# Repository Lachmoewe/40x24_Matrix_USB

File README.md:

40x24_Matrix_USB
================

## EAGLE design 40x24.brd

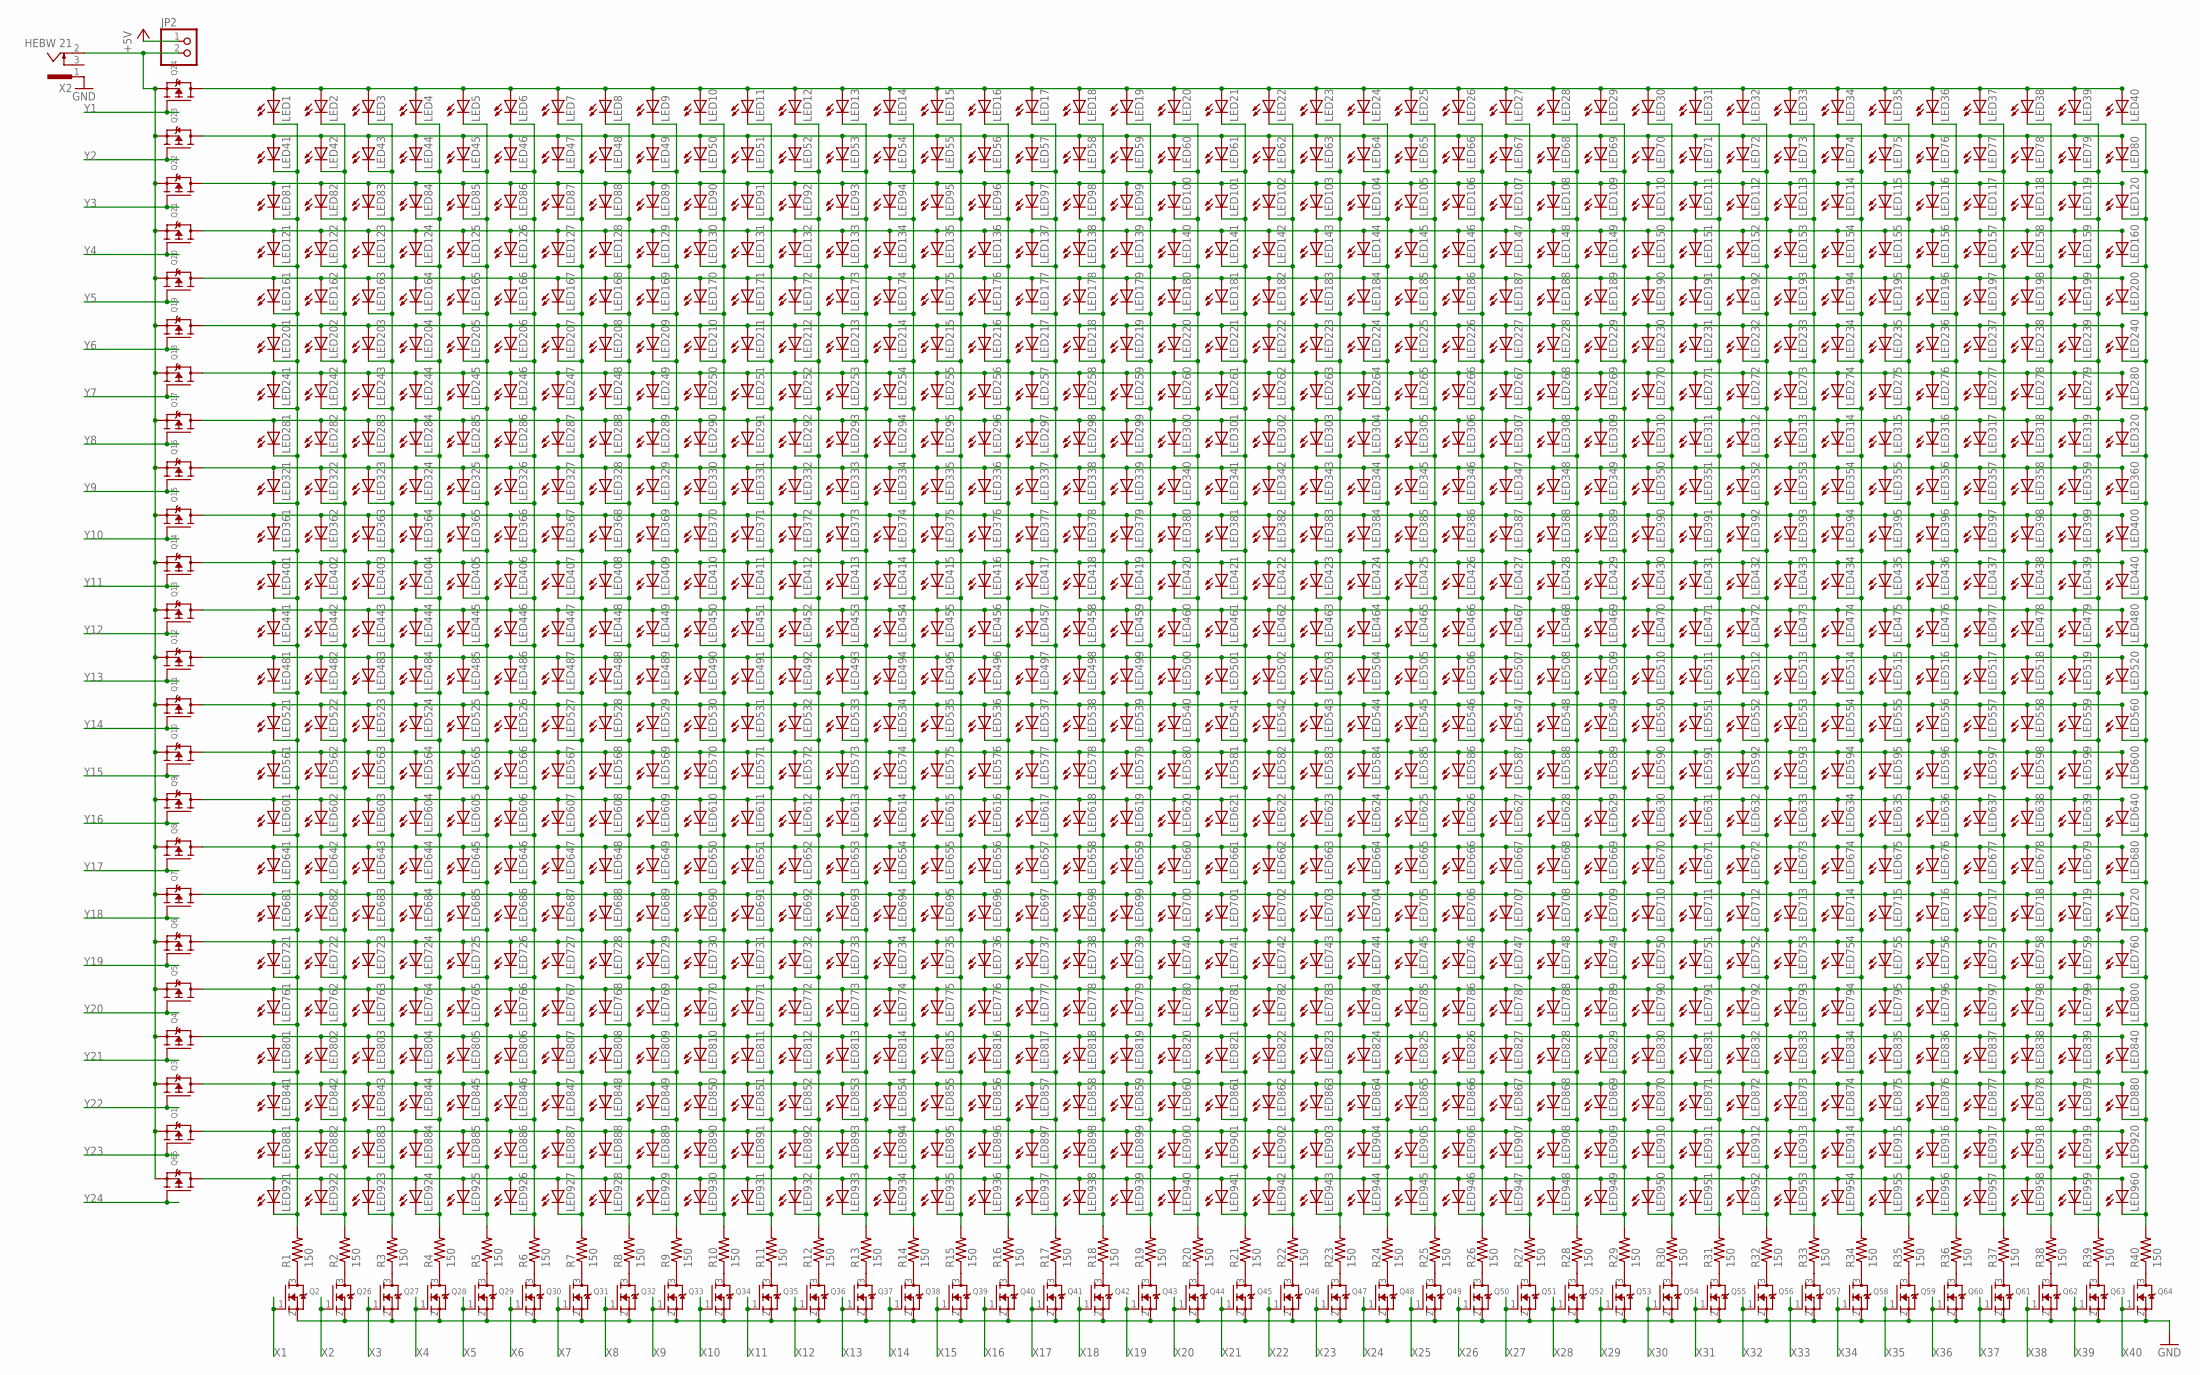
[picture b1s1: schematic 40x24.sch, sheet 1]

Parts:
JP2: PINHD-1X2; 1X02
LED1, LED2, LED3, LED4, LED5, LED6, LED7, LED8, LED9, LED10, LED11, LED12, LED13, LED14, LED15, LED16, LED17, LED18, LED19, LED20, LED21, LED22, LED23, LED24, LED25, LED26, LED27, LED28, LED29, LED30, LED31, LED32, LED33, LED34, LED35, LED36, LED37, LED38, LED39, LED40, LED41, LED42, LED43, LED44, LED45, LED46, LED47, LED48, LED49, LED50, LED51, LED52, LED53, LED54, LED55, LED56, LED57, LED58, LED59, LED60, LED61, LED62, LED63, LED64, LED65, LED66, LED67, LED68, LED69, LED70, LED71, LED72, LED73, LED74, LED75, LED76, LED77, LED78, LED79, LED80, LED81, LED82, LED83, LED84, LED85, LED86, LED87, LED88, LED89, LED90, LED91, LED92, LED93, LED94, LED95, LED96, LED97, LED98, LED99, LED100, LED101, LED102, LED103, LED104, LED105, LED106, LED107, LED108, LED109, LED110, LED111, LED112, LED113, LED114, LED115, LED116, LED117, LED118, LED119, LED120, LED121, LED122, LED123, LED124, LED125, LED126, LED127, LED128, LED129, LED130, LED131, LED132, LED133, LED134, LED135, LED136, LED137, LED138, LED139, LED140, LED141, LED142, LED143, LED144, LED145, LED146, LED147, LED148, LED149, LED150, LED151, LED152, LED153, LED154, LED155, LED156, LED157, LED158, LED159, LED160, LED161, LED162, LED163, LED164, LED165, LED166, LED167, LED168, LED169, LED170, LED171, LED172, LED173, LED174, LED175, LED176, LED177, LED178, LED179, LED180, LED181, LED182, LED183, LED184, LED185, LED186, LED187, LED188, LED189, LED190, LED191, LED192, LED193, LED194, LED195, LED196, LED197, LED198, LED199, LED200, LED201, LED202, LED203, LED204, LED205, LED206, LED207, LED208, LED209, LED210, LED211, LED212, LED213, LED214, LED215, LED216, LED217, LED218, LED219, LED220, LED221, LED222, LED223, LED224, LED225, LED226, LED227, LED228, LED229, LED230, LED231, LED232, LED233, LED234, LED235, LED236, LED237, LED238, LED239, LED240, LED241, LED242, LED243, LED244, LED245, LED246, LED247, LED248, LED249, LED250, LED251, LED252, LED253, LED254, LED255, LED256, LED257, LED258, LED259, LED260, LED261, LED262, LED263, LED264, LED265, LED266, LED267, LED268, LED269, LED270, LED271, LED272, LED273, LED274, LED275, LED276, LED277, LED278, LED279, LED280, LED281, LED282, LED283, LED284, LED285, LED286, LED287, LED288, LED289, LED290, LED291, LED292, LED293, LED294, LED295, LED296, LED297, LED298, LED299, LED300, LED301, LED302, LED303, LED304, LED305, LED306, LED307, LED308, LED309, LED310, LED311, LED312, LED313, LED314, LED315, LED316, LED317, LED318, LED319, LED320, LED321, LED322, LED323, LED324, LED325, LED326, LED327, LED328, LED329, LED330, LED331, LED332, LED333, LED334, LED335, LED336, LED337, LED338, LED339, LED340, LED341, LED342, LED343, LED344, LED345, LED346, LED347, LED348, LED349, LED350, LED351, LED352, LED353, LED354, LED355, LED356, LED357, LED358, LED359, LED360, LED361, LED362, LED363, LED364, LED365, LED366, LED367, LED368, LED369, LED370, LED371, LED372, LED373, LED374, LED375, LED376, LED377, LED378, LED379, LED380, LED381, LED382, LED383, LED384, LED385, LED386, LED387, LED388, LED389, LED390, LED391, LED392, LED393, LED394, LED395, LED396, LED397, LED398, LED399, LED400, LED401, LED402, LED403, LED404, LED405, LED406, LED407, LED408, LED409, LED410, LED411, LED412, LED413, LED414, LED415, LED416, LED417, LED418, LED419, LED420, LED421, LED422, LED423, LED424, LED425, LED426, LED427, LED428, LED429, LED430, LED431, LED432, LED433, LED434, LED435, LED436, LED437, LED438, LED439, LED440, LED441, LED442, LED443, LED444, LED445, LED446, LED447, LED448, LED449, LED450, LED451, LED452, LED453, LED454, LED455, LED456, LED457, LED458, LED459, LED460, LED461, LED462, LED463, LED464, LED465, LED466, LED467, LED468, LED469, LED470, LED471, LED472, LED473, LED474, LED475, LED476, LED477, LED478, LED479, LED480, LED481, LED482, LED483, LED484, LED485, LED486, LED487, LED488, LED489, LED490, LED491, LED492, LED493, LED494, LED495, LED496, LED497, LED498, LED499, LED500, LED501, LED502, LED503, LED504, LED505, LED506, LED507, LED508, LED509, LED510, LED511, LED512, LED513, LED514, LED515, LED516, LED517, LED518, LED519, LED520, LED521, LED522, LED523, LED524, LED525, LED526, LED527, LED528, LED529, LED530, LED531, LED532, LED533, LED534, LED535, LED536, LED537, LED538, LED539, LED540, LED541, LED542, LED543, LED544, LED545, LED546, LED547, LED548, LED549, LED550, LED551, LED552, LED553, LED554, LED555, LED556, LED557, LED558, LED559, LED560, LED561, LED562, LED563, LED564, LED565, LED566, LED567, LED568, LED569, LED570, LED571, LED572, LED573, LED574, LED575, LED576, LED577, LED578, LED579, LED580, LED581, LED582, LED583, LED584, LED585, LED586, LED587, LED588, LED589, LED590, LED591, LED592, LED593, LED594, LED595, LED596, LED597, LED598, LED599, LED600, LED601, LED602, LED603, LED604, LED605, LED606, LED607, LED608, LED609, LED610, LED611, LED612, LED613, LED614, LED615, LED616, LED617, LED618, LED619, LED620, LED621, LED622, LED623, LED624, LED625, LED626, LED627, LED628, LED629, LED630, LED631, LED632, LED633, LED634, LED635, LED636, LED637, LED638, LED639, LED640, LED641, LED642, LED643, LED644, LED645, LED646, LED647, LED648, LED649, LED650, LED651, LED652, LED653, LED654, LED655, LED656, LED657, LED658, LED659, LED660, LED661, LED662, LED663, LED664, LED665, LED666, LED667, LED668, LED669, LED670, LED671, LED672, LED673, LED674, LED675, LED676, LED677, LED678, LED679, LED680, LED681, LED682, LED683, LED684, LED685, LED686, LED687, LED688, LED689, LED690, LED691, LED692, LED693, LED694, LED695, LED696, LED697, LED698, LED699, LED700, LED701, LED702, LED703, LED704, LED705, LED706, LED707, LED708, LED709, LED710, LED711, LED712, LED713, LED714, LED715, LED716, LED717, LED718, LED719, LED720, LED721, LED722, LED723, LED724, LED725, LED726, LED727, LED728, LED729, LED730, LED731, LED732, LED733, LED734, LED735, LED736, LED737, LED738, LED739, LED740, LED741, LED742, LED743, LED744, LED745, LED746, LED747, LED748, LED749, LED750, LED751, LED752, LED753, LED754, LED755, LED756, LED757, LED758, LED759, LED760, LED761, LED762, LED763, LED764, LED765, LED766, LED767, LED768, LED769, LED770, LED771, LED772, LED773, LED774, LED775, LED776, LED777, LED778, LED779, LED780, LED781, LED782, LED783, LED784, LED785, LED786, LED787, LED788, LED789, LED790, LED791, LED792, LED793, LED794, LED795, LED796, LED797, LED798, LED799, LED800, LED801, LED802, LED803, LED804, LED805, LED806, LED807, LED808, LED809, LED810, LED811, LED812, LED813, LED814, LED815, LED816, LED817, LED818, LED819, LED820, LED821, LED822, LED823, LED824, LED825, LED826, LED827, LED828, LED829, LED830, LED831, LED832, LED833, LED834, LED835, LED836, LED837, LED838, LED839, LED840, LED841, LED842, LED843, LED844, LED845, LED846, LED847, LED848, LED849, LED850, LED851, LED852, LED853, LED854, LED855, LED856, LED857, LED858, LED859, LED860, LED861, LED862, LED863, LED864, LED865, LED866, LED867, LED868, LED869, LED870, LED871, LED872, LED873, LED874, LED875, LED876, LED877, LED878, LED879, LED880, LED881, LED882, LED883, LED884, LED885, LED886, LED887, LED888, LED889, LED890, LED891, LED892, LED893, LED894, LED895, LED896, LED897, LED898, LED899, LED900, LED901, LED902, LED903, LED904, LED905, LED906, LED907, LED908, LED909, LED910, LED911, LED912, LED913, LED914, LED915, LED916, LED917, LED918, LED919, LED920, LED921, LED922, LED923, LED924, LED925, LED926, LED927, LED928, LED929, LED930, LED931, LED932, LED933, LED934, LED935, LED936, LED937, LED938, LED939, LED940, LED941, LED942, LED943, LED944, LED945, LED946, LED947, LED948, LED949, LED950, LED951, LED952, LED953, LED954, LED955, LED956, LED957, LED958, LED959, LED960: LED3MM
Q1, Q3, Q4, Q5, Q6, Q7, Q8, Q9, Q10, Q11, Q12, Q13, Q14, Q15, Q16, Q17, Q18, Q19, Q20, Q21, Q22, Q23, Q24, Q65: MOSFET-P; SOT23-R
Q2, Q26, Q27, Q28, Q29, Q30, Q31, Q32, Q33, Q34, Q35, Q36, Q37, Q38, Q39, Q40, Q41, Q42, Q43, Q44, Q45, Q46, Q47, Q48, Q49, Q50, Q51, Q52, Q53, Q54, Q55, Q56, Q57, Q58, Q59, Q60, Q61, Q62, Q63, Q64: MOSFET-NREFLOW; SOT23-R
R1, R2, R3, R4, R5, R6, R7, R8, R9, R10, R11, R12, R13, R14, R15, R16, R17, R18, R19, R20, R21, R22, R23, R24, R25, R26, R27, R28, R29, R30, R31, R32, R33, R34, R35, R36, R37, R38, R39, R40: 150; 0805
X2: HEBW 21; 733980-62

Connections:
+5V: JP2.1; also elsewhere on the board
GND: Q2.2 (S), Q26.2 (S), Q27.2 (S), Q28.2 (S), Q29.2 (S), Q30.2 (S), Q31.2 (S), Q32.2 (S), Q33.2 (S), Q34.2 (S), Q35.2 (S), Q36.2 (S), Q37.2 (S), Q38.2 (S), Q39.2 (S), Q40.2 (S), Q41.2 (S), Q42.2 (S), Q43.2 (S), Q44.2 (S), Q45.2 (S), Q46.2 (S), Q47.2 (S), Q48.2 (S), Q49.2 (S), Q50.2 (S), Q51.2 (S), Q52.2 (S), Q53.2 (S), Q54.2 (S), Q55.2 (S), Q56.2 (S), Q57.2 (S), Q58.2 (S), Q59.2 (S), Q60.2 (S), Q61.2 (S), Q62.2 (S), Q63.2 (S), Q64.2 (S), X2.1; also elsewhere on the board
unnamed: LED1.A, LED2.A, LED3.A, LED4.A, LED5.A, LED6.A, LED7.A, LED8.A, LED9.A, LED10.A, LED11.A, LED12.A, LED13.A, LED14.A, LED15.A, LED16.A, LED17.A, LED18.A, LED19.A, LED20.A, LED21.A, LED22.A, LED23.A, LED24.A, LED25.A, LED26.A, LED27.A, LED28.A, LED29.A, LED30.A, LED31.A, LED32.A, LED33.A, LED34.A, LED35.A, LED36.A, LED37.A, LED38.A, LED39.A, LED40.A, Q24.3 (D)
unnamed: LED81.A, LED82.A, LED83.A, LED84.A, LED85.A, LED86.A, LED87.A, LED88.A, LED89.A, LED90.A, LED91.A, LED92.A, LED93.A, LED94.A, LED95.A, LED96.A, LED97.A, LED98.A, LED99.A, LED100.A, LED101.A, LED102.A, LED103.A, LED104.A, LED105.A, LED106.A, LED107.A, LED108.A, LED109.A, LED110.A, LED111.A, LED112.A, LED113.A, LED114.A, LED115.A, LED116.A, LED117.A, LED118.A, LED119.A, LED120.A, Q22.3 (D)
unnamed: Q2.3 (D), R1.1
unnamed: Q26.3 (D), R2.1
unnamed: LED2.K (C), LED42.K (C), LED82.K (C), LED122.K (C), LED162.K (C), LED202.K (C), LED242.K (C), LED282.K (C), LED322.K (C), LED362.K (C), LED402.K (C), LED442.K (C), LED482.K (C), LED522.K (C), LED562.K (C), LED602.K (C), LED642.K (C), LED682.K (C), LED722.K (C), LED762.K (C), LED802.K (C), LED842.K (C), LED882.K (C), LED922.K (C), R2.2
unnamed: Q27.3 (D), R3.1
unnamed: Q28.3 (D), R4.1
unnamed: Q29.3 (D), R5.1
unnamed: Q30.3 (D), R6.1
unnamed: Q31.3 (D), R7.1
unnamed: Q32.3 (D), R8.1
unnamed: Q33.3 (D), R9.1
unnamed: Q34.3 (D), R10.1
unnamed: Q35.3 (D), R11.1
unnamed: Q36.3 (D), R12.1
unnamed: Q37.3 (D), R13.1
unnamed: Q38.3 (D), R14.1
unnamed: Q39.3 (D), R15.1
unnamed: Q40.3 (D), R16.1
unnamed: Q41.3 (D), R17.1
unnamed: Q42.3 (D), R18.1
unnamed: Q43.3 (D), R19.1
unnamed: Q44.3 (D), R20.1
unnamed: Q45.3 (D), R21.1
unnamed: Q46.3 (D), R22.1
unnamed: Q47.3 (D), R23.1
unnamed: Q48.3 (D), R24.1
unnamed: Q49.3 (D), R25.1
unnamed: Q50.3 (D), R26.1
unnamed: Q51.3 (D), R27.1
unnamed: Q52.3 (D), R28.1
unnamed: Q53.3 (D), R29.1
unnamed: Q54.3 (D), R30.1
unnamed: Q55.3 (D), R31.1
unnamed: Q56.3 (D), R32.1
unnamed: Q57.3 (D), R33.1
unnamed: Q58.3 (D), R34.1
unnamed: Q59.3 (D), R35.1
unnamed: Q60.3 (D), R36.1
unnamed: LED41.A, LED42.A, LED43.A, LED44.A, LED45.A, LED46.A, LED47.A, LED48.A, LED49.A, LED50.A, LED51.A, LED52.A, LED53.A, LED54.A, LED55.A, LED56.A, LED57.A, LED58.A, LED59.A, LED60.A, LED61.A, LED62.A, LED63.A, LED64.A, LED65.A, LED66.A, LED67.A, LED68.A, LED69.A, LED70.A, LED71.A, LED72.A, LED73.A, LED74.A, LED75.A, LED76.A, LED77.A, LED78.A, LED79.A, LED80.A, Q23.3 (D)
unnamed: Q61.3 (D), R37.1
unnamed: Q62.3 (D), R38.1
unnamed: Q63.3 (D), R39.1
unnamed: Q64.3 (D), R40.1
unnamed: JP2.2, Q1.2 (S), Q3.2 (S), Q4.2 (S), Q5.2 (S), Q6.2 (S), Q7.2 (S), Q8.2 (S), Q9.2 (S), Q10.2 (S), Q11.2 (S), Q12.2 (S), Q13.2 (S), Q14.2 (S), Q15.2 (S), Q16.2 (S), Q17.2 (S), Q18.2 (S), Q19.2 (S), Q20.2 (S), Q21.2 (S), Q22.2 (S), Q23.2 (S), Q24.2 (S), Q65.2 (S), X2.2
unnamed: LED121.A, LED122.A, LED123.A, LED124.A, LED125.A, LED126.A, LED127.A, LED128.A, LED129.A, LED130.A, LED131.A, LED132.A, LED133.A, LED134.A, LED135.A, LED136.A, LED137.A, LED138.A, LED139.A, LED140.A, LED141.A, LED142.A, LED143.A, LED144.A, LED145.A, LED146.A, LED147.A, LED148.A, LED149.A, LED150.A, LED151.A, LED152.A, LED153.A, LED154.A, LED155.A, LED156.A, LED157.A, LED158.A, LED159.A, LED160.A, Q21.3 (D)
unnamed: LED161.A, LED162.A, LED163.A, LED164.A, LED165.A, LED166.A, LED167.A, LED168.A, LED169.A, LED170.A, LED171.A, LED172.A, LED173.A, LED174.A, LED175.A, LED176.A, LED177.A, LED178.A, LED179.A, LED180.A, LED181.A, LED182.A, LED183.A, LED184.A, LED185.A, LED186.A, LED187.A, LED188.A, LED189.A, LED190.A, LED191.A, LED192.A, LED193.A, LED194.A, LED195.A, LED196.A, LED197.A, LED198.A, LED199.A, LED200.A, Q20.3 (D)
unnamed: LED201.A, LED202.A, LED203.A, LED204.A, LED205.A, LED206.A, LED207.A, LED208.A, LED209.A, LED210.A, LED211.A, LED212.A, LED213.A, LED214.A, LED215.A, LED216.A, LED217.A, LED218.A, LED219.A, LED220.A, LED221.A, LED222.A, LED223.A, LED224.A, LED225.A, LED226.A, LED227.A, LED228.A, LED229.A, LED230.A, LED231.A, LED232.A, LED233.A, LED234.A, LED235.A, LED236.A, LED237.A, LED238.A, LED239.A, LED240.A, Q19.3 (D)
unnamed: LED241.A, LED242.A, LED243.A, LED244.A, LED245.A, LED246.A, LED247.A, LED248.A, LED249.A, LED250.A, LED251.A, LED252.A, LED253.A, LED254.A, LED255.A, LED256.A, LED257.A, LED258.A, LED259.A, LED260.A, LED261.A, LED262.A, LED263.A, LED264.A, LED265.A, LED266.A, LED267.A, LED268.A, LED269.A, LED270.A, LED271.A, LED272.A, LED273.A, LED274.A, LED275.A, LED276.A, LED277.A, LED278.A, LED279.A, LED280.A, Q18.3 (D)
unnamed: LED281.A, LED282.A, LED283.A, LED284.A, LED285.A, LED286.A, LED287.A, LED288.A, LED289.A, LED290.A, LED291.A, LED292.A, LED293.A, LED294.A, LED295.A, LED296.A, LED297.A, LED298.A, LED299.A, LED300.A, LED301.A, LED302.A, LED303.A, LED304.A, LED305.A, LED306.A, LED307.A, LED308.A, LED309.A, LED310.A, LED311.A, LED312.A, LED313.A, LED314.A, LED315.A, LED316.A, LED317.A, LED318.A, LED319.A, LED320.A, Q17.3 (D)
unnamed: LED321.A, LED322.A, LED323.A, LED324.A, LED325.A, LED326.A, LED327.A, LED328.A, LED329.A, LED330.A, LED331.A, LED332.A, LED333.A, LED334.A, LED335.A, LED336.A, LED337.A, LED338.A, LED339.A, LED340.A, LED341.A, LED342.A, LED343.A, LED344.A, LED345.A, LED346.A, LED347.A, LED348.A, LED349.A, LED350.A, LED351.A, LED352.A, LED353.A, LED354.A, LED355.A, LED356.A, LED357.A, LED358.A, LED359.A, LED360.A, Q16.3 (D)
unnamed: LED361.A, LED362.A, LED363.A, LED364.A, LED365.A, LED366.A, LED367.A, LED368.A, LED369.A, LED370.A, LED371.A, LED372.A, LED373.A, LED374.A, LED375.A, LED376.A, LED377.A, LED378.A, LED379.A, LED380.A, LED381.A, LED382.A, LED383.A, LED384.A, LED385.A, LED386.A, LED387.A, LED388.A, LED389.A, LED390.A, LED391.A, LED392.A, LED393.A, LED394.A, LED395.A, LED396.A, LED397.A, LED398.A, LED399.A, LED400.A, Q15.3 (D)
unnamed: LED401.A, LED402.A, LED403.A, LED404.A, LED405.A, LED406.A, LED407.A, LED408.A, LED409.A, LED410.A, LED411.A, LED412.A, LED413.A, LED414.A, LED415.A, LED416.A, LED417.A, LED418.A, LED419.A, LED420.A, LED421.A, LED422.A, LED423.A, LED424.A, LED425.A, LED426.A, LED427.A, LED428.A, LED429.A, LED430.A, LED431.A, LED432.A, LED433.A, LED434.A, LED435.A, LED436.A, LED437.A, LED438.A, LED439.A, LED440.A, Q14.3 (D)
unnamed: LED441.A, LED442.A, LED443.A, LED444.A, LED445.A, LED446.A, LED447.A, LED448.A, LED449.A, LED450.A, LED451.A, LED452.A, LED453.A, LED454.A, LED455.A, LED456.A, LED457.A, LED458.A, LED459.A, LED460.A, LED461.A, LED462.A, LED463.A, LED464.A, LED465.A, LED466.A, LED467.A, LED468.A, LED469.A, LED470.A, LED471.A, LED472.A, LED473.A, LED474.A, LED475.A, LED476.A, LED477.A, LED478.A, LED479.A, LED480.A, Q13.3 (D)
unnamed: LED481.A, LED482.A, LED483.A, LED484.A, LED485.A, LED486.A, LED487.A, LED488.A, LED489.A, LED490.A, LED491.A, LED492.A, LED493.A, LED494.A, LED495.A, LED496.A, LED497.A, LED498.A, LED499.A, LED500.A, LED501.A, LED502.A, LED503.A, LED504.A, LED505.A, LED506.A, LED507.A, LED508.A, LED509.A, LED510.A, LED511.A, LED512.A, LED513.A, LED514.A, LED515.A, LED516.A, LED517.A, LED518.A, LED519.A, LED520.A, Q12.3 (D)
unnamed: LED521.A, LED522.A, LED523.A, LED524.A, LED525.A, LED526.A, LED527.A, LED528.A, LED529.A, LED530.A, LED531.A, LED532.A, LED533.A, LED534.A, LED535.A, LED536.A, LED537.A, LED538.A, LED539.A, LED540.A, LED541.A, LED542.A, LED543.A, LED544.A, LED545.A, LED546.A, LED547.A, LED548.A, LED549.A, LED550.A, LED551.A, LED552.A, LED553.A, LED554.A, LED555.A, LED556.A, LED557.A, LED558.A, LED559.A, LED560.A, Q11.3 (D)
unnamed: LED561.A, LED562.A, LED563.A, LED564.A, LED565.A, LED566.A, LED567.A, LED568.A, LED569.A, LED570.A, LED571.A, LED572.A, LED573.A, LED574.A, LED575.A, LED576.A, LED577.A, LED578.A, LED579.A, LED580.A, LED581.A, LED582.A, LED583.A, LED584.A, LED585.A, LED586.A, LED587.A, LED588.A, LED589.A, LED590.A, LED591.A, LED592.A, LED593.A, LED594.A, LED595.A, LED596.A, LED597.A, LED598.A, LED599.A, LED600.A, Q10.3 (D)
unnamed: LED601.A, LED602.A, LED603.A, LED604.A, LED605.A, LED606.A, LED607.A, LED608.A, LED609.A, LED610.A, LED611.A, LED612.A, LED613.A, LED614.A, LED615.A, LED616.A, LED617.A, LED618.A, LED619.A, LED620.A, LED621.A, LED622.A, LED623.A, LED624.A, LED625.A, LED626.A, LED627.A, LED628.A, LED629.A, LED630.A, LED631.A, LED632.A, LED633.A, LED634.A, LED635.A, LED636.A, LED637.A, LED638.A, LED639.A, LED640.A, Q9.3 (D)
unnamed: LED641.A, LED642.A, LED643.A, LED644.A, LED645.A, LED646.A, LED647.A, LED648.A, LED649.A, LED650.A, LED651.A, LED652.A, LED653.A, LED654.A, LED655.A, LED656.A, LED657.A, LED658.A, LED659.A, LED660.A, LED661.A, LED662.A, LED663.A, LED664.A, LED665.A, LED666.A, LED667.A, LED668.A, LED669.A, LED670.A, LED671.A, LED672.A, LED673.A, LED674.A, LED675.A, LED676.A, LED677.A, LED678.A, LED679.A, LED680.A, Q8.3 (D)
unnamed: LED681.A, LED682.A, LED683.A, LED684.A, LED685.A, LED686.A, LED687.A, LED688.A, LED689.A, LED690.A, LED691.A, LED692.A, LED693.A, LED694.A, LED695.A, LED696.A, LED697.A, LED698.A, LED699.A, LED700.A, LED701.A, LED702.A, LED703.A, LED704.A, LED705.A, LED706.A, LED707.A, LED708.A, LED709.A, LED710.A, LED711.A, LED712.A, LED713.A, LED714.A, LED715.A, LED716.A, LED717.A, LED718.A, LED719.A, LED720.A, Q7.3 (D)
unnamed: LED721.A, LED722.A, LED723.A, LED724.A, LED725.A, LED726.A, LED727.A, LED728.A, LED729.A, LED730.A, LED731.A, LED732.A, LED733.A, LED734.A, LED735.A, LED736.A, LED737.A, LED738.A, LED739.A, LED740.A, LED741.A, LED742.A, LED743.A, LED744.A, LED745.A, LED746.A, LED747.A, LED748.A, LED749.A, LED750.A, LED751.A, LED752.A, LED753.A, LED754.A, LED755.A, LED756.A, LED757.A, LED758.A, LED759.A, LED760.A, Q6.3 (D)
unnamed: LED761.A, LED762.A, LED763.A, LED764.A, LED765.A, LED766.A, LED767.A, LED768.A, LED769.A, LED770.A, LED771.A, LED772.A, LED773.A, LED774.A, LED775.A, LED776.A, LED777.A, LED778.A, LED779.A, LED780.A, LED781.A, LED782.A, LED783.A, LED784.A, LED785.A, LED786.A, LED787.A, LED788.A, LED789.A, LED790.A, LED791.A, LED792.A, LED793.A, LED794.A, LED795.A, LED796.A, LED797.A, LED798.A, LED799.A, LED800.A, Q5.3 (D)
unnamed: LED801.A, LED802.A, LED803.A, LED804.A, LED805.A, LED806.A, LED807.A, LED808.A, LED809.A, LED810.A, LED811.A, LED812.A, LED813.A, LED814.A, LED815.A, LED816.A, LED817.A, LED818.A, LED819.A, LED820.A, LED821.A, LED822.A, LED823.A, LED824.A, LED825.A, LED826.A, LED827.A, LED828.A, LED829.A, LED830.A, LED831.A, LED832.A, LED833.A, LED834.A, LED835.A, LED836.A, LED837.A, LED838.A, LED839.A, LED840.A, Q4.3 (D)
unnamed: LED841.A, LED842.A, LED843.A, LED844.A, LED845.A, LED846.A, LED847.A, LED848.A, LED849.A, LED850.A, LED851.A, LED852.A, LED853.A, LED854.A, LED855.A, LED856.A, LED857.A, LED858.A, LED859.A, LED860.A, LED861.A, LED862.A, LED863.A, LED864.A, LED865.A, LED866.A, LED867.A, LED868.A, LED869.A, LED870.A, LED871.A, LED872.A, LED873.A, LED874.A, LED875.A, LED876.A, LED877.A, LED878.A, LED879.A, LED880.A, Q3.3 (D)
unnamed: LED881.A, LED882.A, LED883.A, LED884.A, LED885.A, LED886.A, LED887.A, LED888.A, LED889.A, LED890.A, LED891.A, LED892.A, LED893.A, LED894.A, LED895.A, LED896.A, LED897.A, LED898.A, LED899.A, LED900.A, LED901.A, LED902.A, LED903.A, LED904.A, LED905.A, LED906.A, LED907.A, LED908.A, LED909.A, LED910.A, LED911.A, LED912.A, LED913.A, LED914.A, LED915.A, LED916.A, LED917.A, LED918.A, LED919.A, LED920.A, Q1.3 (D)
unnamed: LED921.A, LED922.A, LED923.A, LED924.A, LED925.A, LED926.A, LED927.A, LED928.A, LED929.A, LED930.A, LED931.A, LED932.A, LED933.A, LED934.A, LED935.A, LED936.A, LED937.A, LED938.A, LED939.A, LED940.A, LED941.A, LED942.A, LED943.A, LED944.A, LED945.A, LED946.A, LED947.A, LED948.A, LED949.A, LED950.A, LED951.A, LED952.A, LED953.A, LED954.A, LED955.A, LED956.A, LED957.A, LED958.A, LED959.A, LED960.A, Q65.3 (D)
unnamed: LED4.K (C), LED44.K (C), LED84.K (C), LED124.K (C), LED164.K (C), LED204.K (C), LED244.K (C), LED284.K (C), LED324.K (C), LED364.K (C), LED404.K (C), LED444.K (C), LED484.K (C), LED524.K (C), LED564.K (C), LED604.K (C), LED644.K (C), LED684.K (C), LED724.K (C), LED764.K (C), LED804.K (C), LED844.K (C), LED884.K (C), LED924.K (C), R4.2
unnamed: LED5.K (C), LED45.K (C), LED85.K (C), LED125.K (C), LED165.K (C), LED205.K (C), LED245.K (C), LED285.K (C), LED325.K (C), LED365.K (C), LED405.K (C), LED445.K (C), LED485.K (C), LED525.K (C), LED565.K (C), LED605.K (C), LED645.K (C), LED685.K (C), LED725.K (C), LED765.K (C), LED805.K (C), LED845.K (C), LED885.K (C), LED925.K (C), R5.2
unnamed: LED6.K (C), LED46.K (C), LED86.K (C), LED126.K (C), LED166.K (C), LED206.K (C), LED246.K (C), LED286.K (C), LED326.K (C), LED366.K (C), LED406.K (C), LED446.K (C), LED486.K (C), LED526.K (C), LED566.K (C), LED606.K (C), LED646.K (C), LED686.K (C), LED726.K (C), LED766.K (C), LED806.K (C), LED846.K (C), LED886.K (C), LED926.K (C), R6.2
unnamed: LED7.K (C), LED47.K (C), LED87.K (C), LED127.K (C), LED167.K (C), LED207.K (C), LED247.K (C), LED287.K (C), LED327.K (C), LED367.K (C), LED407.K (C), LED447.K (C), LED487.K (C), LED527.K (C), LED567.K (C), LED607.K (C), LED647.K (C), LED687.K (C), LED727.K (C), LED767.K (C), LED807.K (C), LED847.K (C), LED887.K (C), LED927.K (C), R7.2
unnamed: LED8.K (C), LED48.K (C), LED88.K (C), LED128.K (C), LED168.K (C), LED208.K (C), LED248.K (C), LED288.K (C), LED328.K (C), LED368.K (C), LED408.K (C), LED448.K (C), LED488.K (C), LED528.K (C), LED568.K (C), LED608.K (C), LED648.K (C), LED688.K (C), LED728.K (C), LED768.K (C), LED808.K (C), LED848.K (C), LED888.K (C), LED928.K (C), R8.2
unnamed: LED9.K (C), LED49.K (C), LED89.K (C), LED129.K (C), LED169.K (C), LED209.K (C), LED249.K (C), LED289.K (C), LED329.K (C), LED369.K (C), LED409.K (C), LED449.K (C), LED489.K (C), LED529.K (C), LED569.K (C), LED609.K (C), LED649.K (C), LED689.K (C), LED729.K (C), LED769.K (C), LED809.K (C), LED849.K (C), LED889.K (C), LED929.K (C), R9.2
unnamed: LED10.K (C), LED50.K (C), LED90.K (C), LED130.K (C), LED170.K (C), LED210.K (C), LED250.K (C), LED290.K (C), LED330.K (C), LED370.K (C), LED410.K (C), LED450.K (C), LED490.K (C), LED530.K (C), LED570.K (C), LED610.K (C), LED650.K (C), LED690.K (C), LED730.K (C), LED770.K (C), LED810.K (C), LED850.K (C), LED890.K (C), LED930.K (C), R10.2
unnamed: LED11.K (C), LED51.K (C), LED91.K (C), LED131.K (C), LED171.K (C), LED211.K (C), LED251.K (C), LED291.K (C), LED331.K (C), LED371.K (C), LED411.K (C), LED451.K (C), LED491.K (C), LED531.K (C), LED571.K (C), LED611.K (C), LED651.K (C), LED691.K (C), LED731.K (C), LED771.K (C), LED811.K (C), LED851.K (C), LED891.K (C), LED931.K (C), R11.2
unnamed: LED1.K (C), LED41.K (C), LED81.K (C), LED121.K (C), LED161.K (C), LED201.K (C), LED241.K (C), LED281.K (C), LED321.K (C), LED361.K (C), LED401.K (C), LED441.K (C), LED481.K (C), LED521.K (C), LED561.K (C), LED601.K (C), LED641.K (C), LED681.K (C), LED721.K (C), LED761.K (C), LED801.K (C), LED841.K (C), LED881.K (C), LED921.K (C), R1.2
unnamed: LED12.K (C), LED52.K (C), LED92.K (C), LED132.K (C), LED172.K (C), LED212.K (C), LED252.K (C), LED292.K (C), LED332.K (C), LED372.K (C), LED412.K (C), LED452.K (C), LED492.K (C), LED532.K (C), LED572.K (C), LED612.K (C), LED652.K (C), LED692.K (C), LED732.K (C), LED772.K (C), LED812.K (C), LED852.K (C), LED892.K (C), LED932.K (C), R12.2
unnamed: LED13.K (C), LED53.K (C), LED93.K (C), LED133.K (C), LED173.K (C), LED213.K (C), LED253.K (C), LED293.K (C), LED333.K (C), LED373.K (C), LED413.K (C), LED453.K (C), LED493.K (C), LED533.K (C), LED573.K (C), LED613.K (C), LED653.K (C), LED693.K (C), LED733.K (C), LED773.K (C), LED813.K (C), LED853.K (C), LED893.K (C), LED933.K (C), R13.2
unnamed: LED14.K (C), LED54.K (C), LED94.K (C), LED134.K (C), LED174.K (C), LED214.K (C), LED254.K (C), LED294.K (C), LED334.K (C), LED374.K (C), LED414.K (C), LED454.K (C), LED494.K (C), LED534.K (C), LED574.K (C), LED614.K (C), LED654.K (C), LED694.K (C), LED734.K (C), LED774.K (C), LED814.K (C), LED854.K (C), LED894.K (C), LED934.K (C), R14.2
unnamed: LED15.K (C), LED55.K (C), LED95.K (C), LED135.K (C), LED175.K (C), LED215.K (C), LED255.K (C), LED295.K (C), LED335.K (C), LED375.K (C), LED415.K (C), LED455.K (C), LED495.K (C), LED535.K (C), LED575.K (C), LED615.K (C), LED655.K (C), LED695.K (C), LED735.K (C), LED775.K (C), LED815.K (C), LED855.K (C), LED895.K (C), LED935.K (C), R15.2
unnamed: LED16.K (C), LED56.K (C), LED96.K (C), LED136.K (C), LED176.K (C), LED216.K (C), LED256.K (C), LED296.K (C), LED336.K (C), LED376.K (C), LED416.K (C), LED456.K (C), LED496.K (C), LED536.K (C), LED576.K (C), LED616.K (C), LED656.K (C), LED696.K (C), LED736.K (C), LED776.K (C), LED816.K (C), LED856.K (C), LED896.K (C), LED936.K (C), R16.2
unnamed: LED17.K (C), LED57.K (C), LED97.K (C), LED137.K (C), LED177.K (C), LED217.K (C), LED257.K (C), LED297.K (C), LED337.K (C), LED377.K (C), LED417.K (C), LED457.K (C), LED497.K (C), LED537.K (C), LED577.K (C), LED617.K (C), LED657.K (C), LED697.K (C), LED737.K (C), LED777.K (C), LED817.K (C), LED857.K (C), LED897.K (C), LED937.K (C), R17.2
unnamed: LED18.K (C), LED58.K (C), LED98.K (C), LED138.K (C), LED178.K (C), LED218.K (C), LED258.K (C), LED298.K (C), LED338.K (C), LED378.K (C), LED418.K (C), LED458.K (C), LED498.K (C), LED538.K (C), LED578.K (C), LED618.K (C), LED658.K (C), LED698.K (C), LED738.K (C), LED778.K (C), LED818.K (C), LED858.K (C), LED898.K (C), LED938.K (C), R18.2
unnamed: LED19.K (C), LED59.K (C), LED99.K (C), LED139.K (C), LED179.K (C), LED219.K (C), LED259.K (C), LED299.K (C), LED339.K (C), LED379.K (C), LED419.K (C), LED459.K (C), LED499.K (C), LED539.K (C), LED579.K (C), LED619.K (C), LED659.K (C), LED699.K (C), LED739.K (C), LED779.K (C), LED819.K (C), LED859.K (C), LED899.K (C), LED939.K (C), R19.2
unnamed: LED20.K (C), LED60.K (C), LED100.K (C), LED140.K (C), LED180.K (C), LED220.K (C), LED260.K (C), LED300.K (C), LED340.K (C), LED380.K (C), LED420.K (C), LED460.K (C), LED500.K (C), LED540.K (C), LED580.K (C), LED620.K (C), LED660.K (C), LED700.K (C), LED740.K (C), LED780.K (C), LED820.K (C), LED860.K (C), LED900.K (C), LED940.K (C), R20.2
unnamed: LED21.K (C), LED61.K (C), LED101.K (C), LED141.K (C), LED181.K (C), LED221.K (C), LED261.K (C), LED301.K (C), LED341.K (C), LED381.K (C), LED421.K (C), LED461.K (C), LED501.K (C), LED541.K (C), LED581.K (C), LED621.K (C), LED661.K (C), LED701.K (C), LED741.K (C), LED781.K (C), LED821.K (C), LED861.K (C), LED901.K (C), LED941.K (C), R21.2
unnamed: LED22.K (C), LED62.K (C), LED102.K (C), LED142.K (C), LED182.K (C), LED222.K (C), LED262.K (C), LED302.K (C), LED342.K (C), LED382.K (C), LED422.K (C), LED462.K (C), LED502.K (C), LED542.K (C), LED582.K (C), LED622.K (C), LED662.K (C), LED702.K (C), LED742.K (C), LED782.K (C), LED822.K (C), LED862.K (C), LED902.K (C), LED942.K (C), R22.2
unnamed: LED23.K (C), LED63.K (C), LED103.K (C), LED143.K (C), LED183.K (C), LED223.K (C), LED263.K (C), LED303.K (C), LED343.K (C), LED383.K (C), LED423.K (C), LED463.K (C), LED503.K (C), LED543.K (C), LED583.K (C), LED623.K (C), LED663.K (C), LED703.K (C), LED743.K (C), LED783.K (C), LED823.K (C), LED863.K (C), LED903.K (C), LED943.K (C), R23.2
unnamed: LED24.K (C), LED64.K (C), LED104.K (C), LED144.K (C), LED184.K (C), LED224.K (C), LED264.K (C), LED304.K (C), LED344.K (C), LED384.K (C), LED424.K (C), LED464.K (C), LED504.K (C), LED544.K (C), LED584.K (C), LED624.K (C), LED664.K (C), LED704.K (C), LED744.K (C), LED784.K (C), LED824.K (C), LED864.K (C), LED904.K (C), LED944.K (C), R24.2
unnamed: LED25.K (C), LED65.K (C), LED105.K (C), LED145.K (C), LED185.K (C), LED225.K (C), LED265.K (C), LED305.K (C), LED345.K (C), LED385.K (C), LED425.K (C), LED465.K (C), LED505.K (C), LED545.K (C), LED585.K (C), LED625.K (C), LED665.K (C), LED705.K (C), LED745.K (C), LED785.K (C), LED825.K (C), LED865.K (C), LED905.K (C), LED945.K (C), R25.2
unnamed: LED26.K (C), LED66.K (C), LED106.K (C), LED146.K (C), LED186.K (C), LED226.K (C), LED266.K (C), LED306.K (C), LED346.K (C), LED386.K (C), LED426.K (C), LED466.K (C), LED506.K (C), LED546.K (C), LED586.K (C), LED626.K (C), LED666.K (C), LED706.K (C), LED746.K (C), LED786.K (C), LED826.K (C), LED866.K (C), LED906.K (C), LED946.K (C), R26.2
unnamed: LED27.K (C), LED67.K (C), LED107.K (C), LED147.K (C), LED187.K (C), LED227.K (C), LED267.K (C), LED307.K (C), LED347.K (C), LED387.K (C), LED427.K (C), LED467.K (C), LED507.K (C), LED547.K (C), LED587.K (C), LED627.K (C), LED667.K (C), LED707.K (C), LED747.K (C), LED787.K (C), LED827.K (C), LED867.K (C), LED907.K (C), LED947.K (C), R27.2
unnamed: LED28.K (C), LED68.K (C), LED108.K (C), LED148.K (C), LED188.K (C), LED228.K (C), LED268.K (C), LED308.K (C), LED348.K (C), LED388.K (C), LED428.K (C), LED468.K (C), LED508.K (C), LED548.K (C), LED588.K (C), LED628.K (C), LED668.K (C), LED708.K (C), LED748.K (C), LED788.K (C), LED828.K (C), LED868.K (C), LED908.K (C), LED948.K (C), R28.2
unnamed: LED29.K (C), LED69.K (C), LED109.K (C), LED149.K (C), LED189.K (C), LED229.K (C), LED269.K (C), LED309.K (C), LED349.K (C), LED389.K (C), LED429.K (C), LED469.K (C), LED509.K (C), LED549.K (C), LED589.K (C), LED629.K (C), LED669.K (C), LED709.K (C), LED749.K (C), LED789.K (C), LED829.K (C), LED869.K (C), LED909.K (C), LED949.K (C), R29.2
unnamed: LED30.K (C), LED70.K (C), LED110.K (C), LED150.K (C), LED190.K (C), LED230.K (C), LED270.K (C), LED310.K (C), LED350.K (C), LED390.K (C), LED430.K (C), LED470.K (C), LED510.K (C), LED550.K (C), LED590.K (C), LED630.K (C), LED670.K (C), LED710.K (C), LED750.K (C), LED790.K (C), LED830.K (C), LED870.K (C), LED910.K (C), LED950.K (C), R30.2
unnamed: LED31.K (C), LED71.K (C), LED111.K (C), LED151.K (C), LED191.K (C), LED231.K (C), LED271.K (C), LED311.K (C), LED351.K (C), LED391.K (C), LED431.K (C), LED471.K (C), LED511.K (C), LED551.K (C), LED591.K (C), LED631.K (C), LED671.K (C), LED711.K (C), LED751.K (C), LED791.K (C), LED831.K (C), LED871.K (C), LED911.K (C), LED951.K (C), R31.2
unnamed: LED32.K (C), LED72.K (C), LED112.K (C), LED152.K (C), LED192.K (C), LED232.K (C), LED272.K (C), LED312.K (C), LED352.K (C), LED392.K (C), LED432.K (C), LED472.K (C), LED512.K (C), LED552.K (C), LED592.K (C), LED632.K (C), LED672.K (C), LED712.K (C), LED752.K (C), LED792.K (C), LED832.K (C), LED872.K (C), LED912.K (C), LED952.K (C), R32.2
unnamed: LED33.K (C), LED73.K (C), LED113.K (C), LED153.K (C), LED193.K (C), LED233.K (C), LED273.K (C), LED313.K (C), LED353.K (C), LED393.K (C), LED433.K (C), LED473.K (C), LED513.K (C), LED553.K (C), LED593.K (C), LED633.K (C), LED673.K (C), LED713.K (C), LED753.K (C), LED793.K (C), LED833.K (C), LED873.K (C), LED913.K (C), LED953.K (C), R33.2
unnamed: LED34.K (C), LED74.K (C), LED114.K (C), LED154.K (C), LED194.K (C), LED234.K (C), LED274.K (C), LED314.K (C), LED354.K (C), LED394.K (C), LED434.K (C), LED474.K (C), LED514.K (C), LED554.K (C), LED594.K (C), LED634.K (C), LED674.K (C), LED714.K (C), LED754.K (C), LED794.K (C), LED834.K (C), LED874.K (C), LED914.K (C), LED954.K (C), R34.2
unnamed: LED35.K (C), LED75.K (C), LED115.K (C), LED155.K (C), LED195.K (C), LED235.K (C), LED275.K (C), LED315.K (C), LED355.K (C), LED395.K (C), LED435.K (C), LED475.K (C), LED515.K (C), LED555.K (C), LED595.K (C), LED635.K (C), LED675.K (C), LED715.K (C), LED755.K (C), LED795.K (C), LED835.K (C), LED875.K (C), LED915.K (C), LED955.K (C), R35.2
unnamed: LED36.K (C), LED76.K (C), LED116.K (C), LED156.K (C), LED196.K (C), LED236.K (C), LED276.K (C), LED316.K (C), LED356.K (C), LED396.K (C), LED436.K (C), LED476.K (C), LED516.K (C), LED556.K (C), LED596.K (C), LED636.K (C), LED676.K (C), LED716.K (C), LED756.K (C), LED796.K (C), LED836.K (C), LED876.K (C), LED916.K (C), LED956.K (C), R36.2
unnamed: LED37.K (C), LED77.K (C), LED117.K (C), LED157.K (C), LED197.K (C), LED237.K (C), LED277.K (C), LED317.K (C), LED357.K (C), LED397.K (C), LED437.K (C), LED477.K (C), LED517.K (C), LED557.K (C), LED597.K (C), LED637.K (C), LED677.K (C), LED717.K (C), LED757.K (C), LED797.K (C), LED837.K (C), LED877.K (C), LED917.K (C), LED957.K (C), R37.2
unnamed: LED38.K (C), LED78.K (C), LED118.K (C), LED158.K (C), LED198.K (C), LED238.K (C), LED278.K (C), LED318.K (C), LED358.K (C), LED398.K (C), LED438.K (C), LED478.K (C), LED518.K (C), LED558.K (C), LED598.K (C), LED638.K (C), LED678.K (C), LED718.K (C), LED758.K (C), LED798.K (C), LED838.K (C), LED878.K (C), LED918.K (C), LED958.K (C), R38.2
unnamed: LED39.K (C), LED79.K (C), LED119.K (C), LED159.K (C), LED199.K (C), LED239.K (C), LED279.K (C), LED319.K (C), LED359.K (C), LED399.K (C), LED439.K (C), LED479.K (C), LED519.K (C), LED559.K (C), LED599.K (C), LED639.K (C), LED679.K (C), LED719.K (C), LED759.K (C), LED799.K (C), LED839.K (C), LED879.K (C), LED919.K (C), LED959.K (C), R39.2
unnamed: LED40.K (C), LED80.K (C), LED120.K (C), LED160.K (C), LED200.K (C), LED240.K (C), LED280.K (C), LED320.K (C), LED360.K (C), LED400.K (C), LED440.K (C), LED480.K (C), LED520.K (C), LED560.K (C), LED600.K (C), LED640.K (C), LED680.K (C), LED720.K (C), LED760.K (C), LED800.K (C), LED840.K (C), LED880.K (C), LED920.K (C), LED960.K (C), R40.2
unnamed: LED3.K (C), LED43.K (C), LED83.K (C), LED123.K (C), LED163.K (C), LED203.K (C), LED243.K (C), LED283.K (C), LED323.K (C), LED363.K (C), LED403.K (C), LED443.K (C), LED483.K (C), LED523.K (C), LED563.K (C), LED603.K (C), LED643.K (C), LED683.K (C), LED723.K (C), LED763.K (C), LED803.K (C), LED843.K (C), LED883.K (C), LED923.K (C), R3.2
X1: Q2.1 (G); also elsewhere on the board
X2: Q26.1 (G); also elsewhere on the board
X3: Q27.1 (G); also elsewhere on the board
X4: Q28.1 (G); also elsewhere on the board
X5: Q29.1 (G); also elsewhere on the board
X6: Q30.1 (G); also elsewhere on the board
X7: Q31.1 (G); also elsewhere on the board
X8: Q32.1 (G); also elsewhere on the board
X9: Q33.1 (G); also elsewhere on the board
X10: Q34.1 (G); also elsewhere on the board
X11: Q35.1 (G); also elsewhere on the board
X12: Q36.1 (G); also elsewhere on the board
X13: Q37.1 (G); also elsewhere on the board
X14: Q38.1 (G); also elsewhere on the board
X15: Q39.1 (G); also elsewhere on the board
X16: Q40.1 (G); also elsewhere on the board
X17: Q41.1 (G); also elsewhere on the board
X18: Q42.1 (G); also elsewhere on the board
X19: Q43.1 (G); also elsewhere on the board
X20: Q44.1 (G); also elsewhere on the board
X21: Q45.1 (G); also elsewhere on the board
X22: Q46.1 (G); also elsewhere on the board
X23: Q47.1 (G); also elsewhere on the board
X24: Q48.1 (G); also elsewhere on the board
X25: Q49.1 (G); also elsewhere on the board
X26: Q50.1 (G); also elsewhere on the board
X27: Q51.1 (G); also elsewhere on the board
X28: Q52.1 (G); also elsewhere on the board
X29: Q53.1 (G); also elsewhere on the board
X30: Q54.1 (G); also elsewhere on the board
X31: Q55.1 (G); also elsewhere on the board
X32: Q56.1 (G); also elsewhere on the board
X33: Q57.1 (G); also elsewhere on the board
X34: Q58.1 (G); also elsewhere on the board
X35: Q59.1 (G); also elsewhere on the board
X36: Q60.1 (G); also elsewhere on the board
X37: Q61.1 (G); also elsewhere on the board
X38: Q62.1 (G); also elsewhere on the board
X39: Q63.1 (G); also elsewhere on the board
X40: Q64.1 (G); also elsewhere on the board
Y1: Q24.1 (G); also elsewhere on the board
Y2: Q23.1 (G); also elsewhere on the board
Y3: Q22.1 (G); also elsewhere on the board
Y4: Q21.1 (G); also elsewhere on the board
Y5: Q20.1 (G); also elsewhere on the board
Y6: Q19.1 (G); also elsewhere on the board
Y7: Q18.1 (G); also elsewhere on the board
Y8: Q17.1 (G); also elsewhere on the board
Y9: Q16.1 (G); also elsewhere on the board
Y10: Q15.1 (G); also elsewhere on the board
Y11: Q14.1 (G); also elsewhere on the board
Y12: Q13.1 (G); also elsewhere on the board
Y13: Q12.1 (G); also elsewhere on the board
Y14: Q11.1 (G); also elsewhere on the board
Y15: Q10.1 (G); also elsewhere on the board
Y16: Q9.1 (G); also elsewhere on the board
Y17: Q8.1 (G); also elsewhere on the board
Y18: Q7.1 (G); also elsewhere on the board
Y19: Q6.1 (G); also elsewhere on the board
Y20: Q5.1 (G); also elsewhere on the board
Y21: Q4.1 (G); also elsewhere on the board
Y22: Q3.1 (G); also elsewhere on the board
Y23: Q1.1 (G); also elsewhere on the board
Y24: Q65.1 (G); also elsewhere on the board

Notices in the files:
parts and their libraries:
SparkFun: Licensing: CC v3.0 Share-Alike You are welcome to use this library for commercial purposes.
